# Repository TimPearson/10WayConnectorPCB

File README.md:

# 10WayConnectorPCB
A 10 way connector PCB which sits  between a series of LED PCBs and a driver PCB on a PiZero

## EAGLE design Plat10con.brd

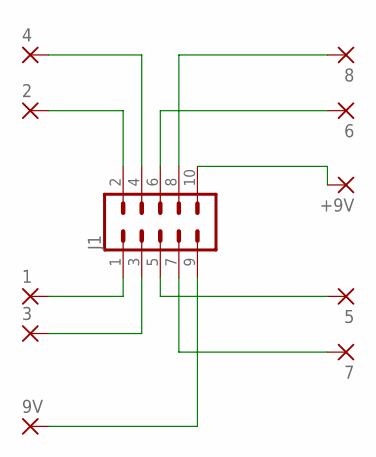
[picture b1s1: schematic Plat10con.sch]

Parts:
1, 2, 3, 4, 5, 6, 7, 8, 9V: 1,6/0,9
+9V: 1,6/0,9
J1: CONN_05X2SHD; 2X5-SHROUDED

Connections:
unnamed: 4.1, J1.4
unnamed: 2.1, J1.2
unnamed: 1.1, J1.1
unnamed: 3.1, J1.3
unnamed: 9V.1, J1.9
unnamed: 5.1, J1.5
unnamed: 7.1, J1.7
unnamed: 6.1, J1.6
unnamed: 8.1, J1.8
unnamed: +9V.1, J1.10

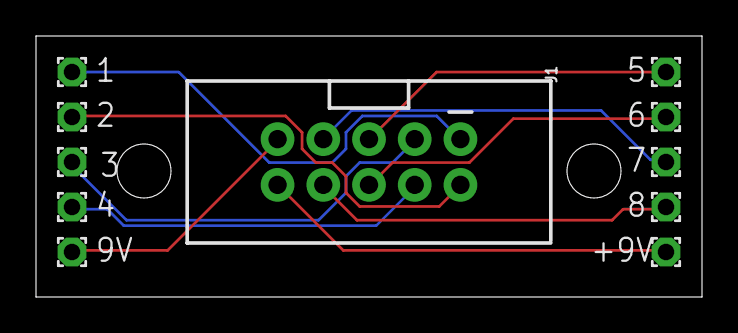
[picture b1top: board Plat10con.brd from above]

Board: 2 copper layers, 37.0 x 14.5 mm, 11 parts (0 on the bottom side), 10 nets.

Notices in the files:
parts and their libraries:
SparkFun-Connectors: Licensing: Creative Commons ShareAlike 4.0 International - https://creativecommons.org/licenses/by-sa/4.0
